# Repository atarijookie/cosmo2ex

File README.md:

# Cosmo2ex
This is a continuation / evolution of CosmosEx device. It is an ACSI/SCSI hard drive emulator, floppy emulator, IKBD emulator for Atari 16/32 Bit range of computers

Open design, non-commercial license - see [License](#license).

# What's what

- ce_cores - this is the network server to which the device connects to
- ce_dd_bootsectors	- ACSI/SCSI boot sectors
- ce_dd_prg	- driver for translated/network drives, date setting and screenshots
- android - Android app for switching floppy images from a phone, with a home screen widget
- docker - build and run scripts for ce_cores and webserver running in docker container
- release - builds tarballs + install script for installing directly on a Linux machine (systemd service)
- webserver - a configuration interface via browser

- libacsiscsi - library for access to ACSI/SCSI interface via few functions
- libdospath - long-to-short filename conversion library, emulating DOS paths (8.3)

- test_ce	- Atari test tools, all built into a single app (ce_tests.tos) with a menu to pick the test:
  - test_acsi	- Atari ACSI/SCSI transfer tester
  - test_filesystem	- Atari filesystem tester
  - test_floppy	- Atari floppy emulation tester
  - test_floppy_read	- Atari another floppy emulation tester
  - test_ikbd	- Atari IKBD injection chain tester
  - test_manual, test_manual2	- Atari another ACSI/SCSI transfer testers
  - test_rw, test_rw_user	- Atari ACSI write/read verification testers

# Android floppy app

`android/` is an app for switching floppy images from a phone, with a home screen widget. `android/build.sh` builds it in
docker into `webserver/static/app/`; users get it and connect it on the webserver's Settings → Android app. See `android/README.md`.

# Unit tests

`make test` runs all of them (see the top level `Makefile`, CI runs the same in `.github/workflows/ci.yml`).

- Linux: needs `g++`, `make`, `go` and the `libudev-dev` + `libevdev-dev` packages
- Windows: install [Cygwin](https://www.cygwin.com/) with the `gcc-g++` and `make` packages, then in the Cygwin shell:

      make -C libdospath test
      make -C ce_cores test

  Check out the repository with LF line endings (`git config --global core.autocrlf input` before cloning).
- macOS: needs the Xcode command line tools (`xcode-select --install`), then the same two `make` commands as for Windows

The file tests create their files in `/tmp`. Set `CE_TEST_TMPDIR` to run them on another filesystem, e.g. a
case-insensitive one (like APFS on macOS, FAT or NTFS): `CE_TEST_TMPDIR=/mnt/usb make -C libdospath test`.

# License

Cosmo2ex is open design, non-commercial license: the sources and the hardware designs are public, you can build
it, change it and share it for non-commercial use, but not sell it.

- software and firmware - [PolyForm Noncommercial License 1.0.0](LICENSE)
- hardware designs (schematics, PCBs in `devices/`) - [CC BY-NC-SA 4.0](devices/LICENSE)
- third party code keeps its own license (`third_party/`, and the files that say so in their header)

Building devices for yourself or your friends is fine. Selling devices, kits, PCBs or flashed boards needs a written
commercial license from the author - get in touch first (https://joo.kie.sk).

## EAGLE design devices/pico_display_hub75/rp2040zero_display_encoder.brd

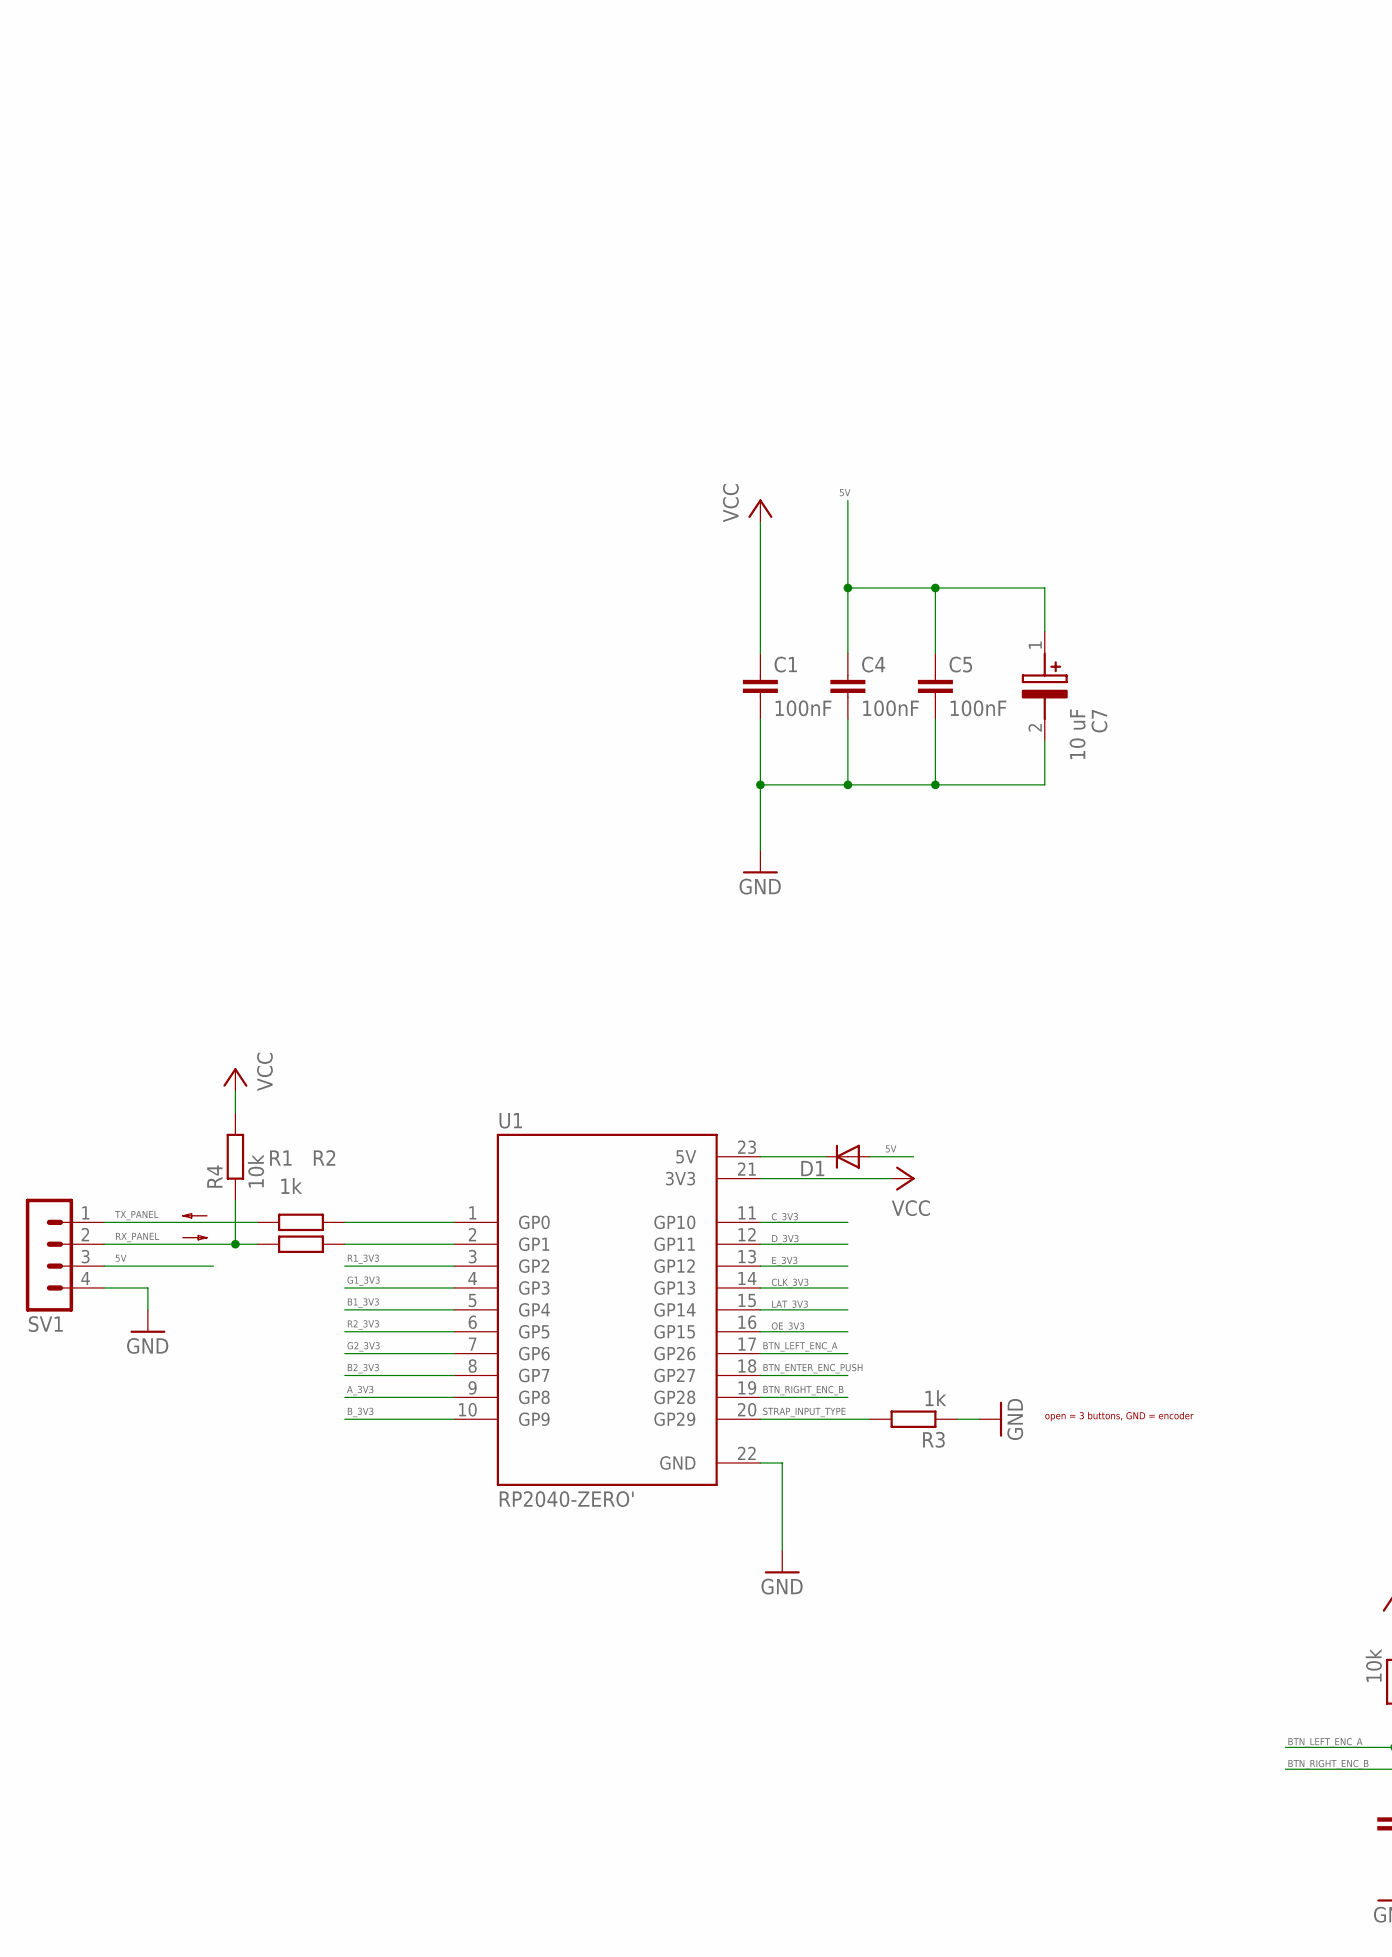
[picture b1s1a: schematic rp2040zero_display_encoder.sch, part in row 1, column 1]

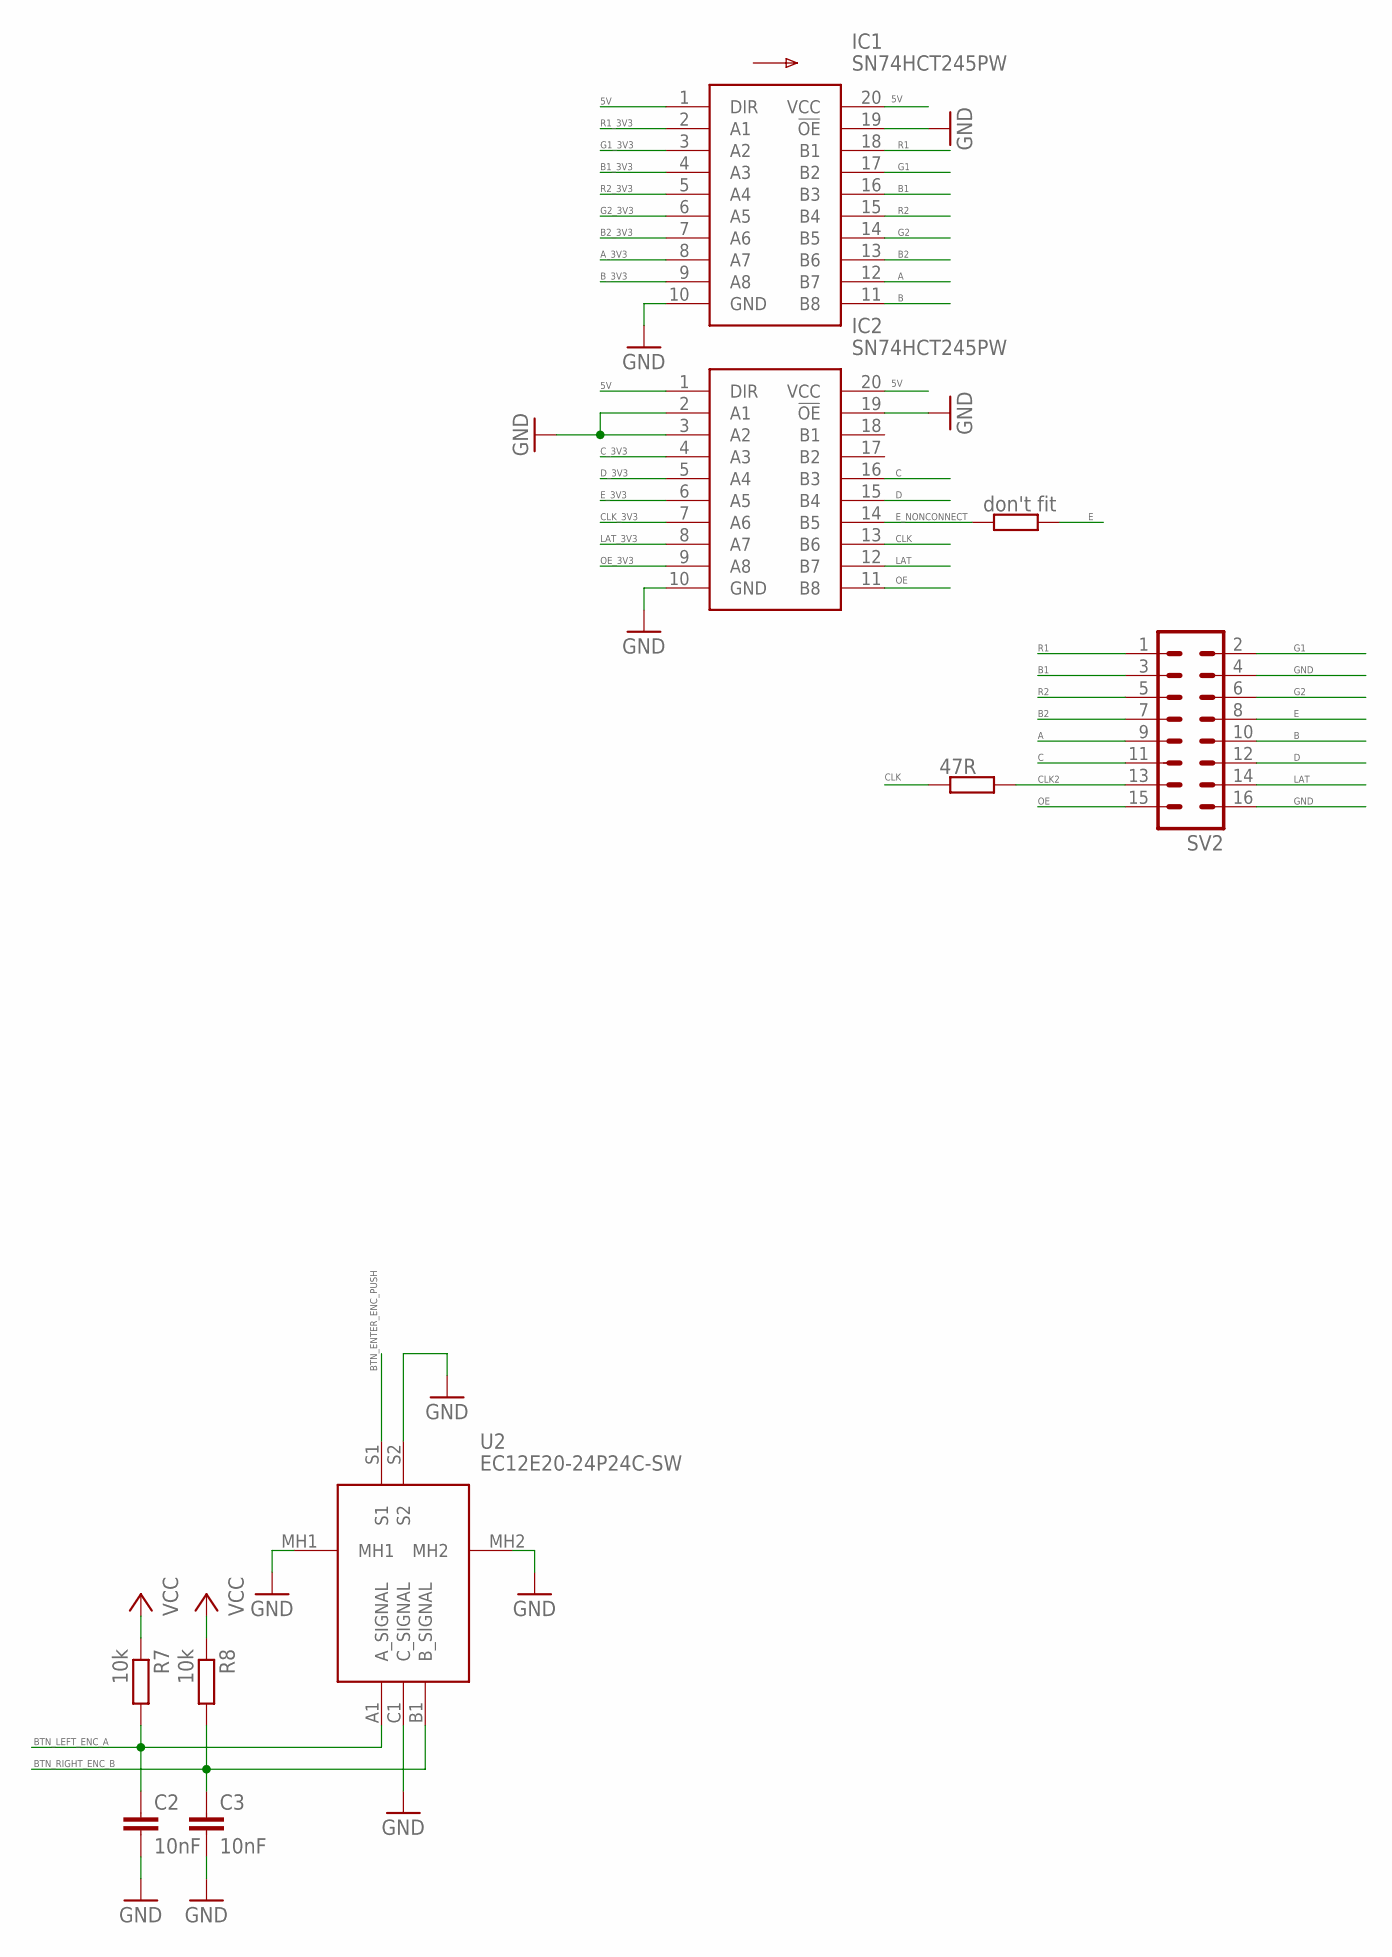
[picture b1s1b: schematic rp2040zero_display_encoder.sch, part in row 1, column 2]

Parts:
C1, C4, C5: 100nF; C0603
C2, C3: 10nF; C0603
C7: 10 uF; CAPPM3528X210N
D1: SK110-DIO; DO214AC
IC1, IC2: SN74HCT245PW; SOP65P640X120-20N
R1, R2, R3: 1k; R0603
R4, R7, R8: 10k; R0603
R5: don't fit; R0603
R6: 47R; R0603
SV1: MA04-1
SV2: ML16
U1: RP2040-ZERO'; MODULE_RP2040-ZERO
U2: EC12E20-24P24C-SW; EC12E2024P24CSW

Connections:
5V: C4.1, C5.1, C7.1 (+), D1.A, IC1.1 (DIR), IC1.20 (VCC), IC2.1 (DIR), IC2.20 (VCC), SV1.3
A: IC1.12 (B7), SV2.9
A_3V3: IC1.8 (A7), U1.9 (GP8)
B: IC1.11 (B8), SV2.10
B1: IC1.16 (B3), SV2.3
B1_3V3: IC1.4 (A3), U1.5 (GP4)
B2: IC1.13 (B6), SV2.7
B2_3V3: IC1.7 (A6), U1.8 (GP7)
BTN_ENTER_ENC_PUSH: U1.18 (GP27), U2.S1
BTN_LEFT_ENC_A: C2.1, R7.2, U1.17 (GP26), U2.A1 (A_SIGNAL)
BTN_RIGHT_ENC_B: C3.1, R8.2, U1.19 (GP28), U2.B1 (B_SIGNAL)
B_3V3: IC1.9 (A8), U1.10 (GP9)
C: IC2.16 (B3), SV2.11
CLK: IC2.13 (B6), R6.1
CLK2: R6.2, SV2.13
CLK_3V3: IC2.7 (A6), U1.14 (GP13)
C_3V3: IC2.4 (A3), U1.11 (GP10)
D: IC2.15 (B4), SV2.12
D_3V3: IC2.5 (A4), U1.12 (GP11)
E: R5.2, SV2.8
E_3V3: IC2.6 (A5), U1.13 (GP12)
E_NONCONNECT: IC2.14 (B5), R5.1
G1: IC1.17 (B2), SV2.2
G1_3V3: IC1.3 (A2), U1.4 (GP3)
G2: IC1.14 (B5), SV2.6
G2_3V3: IC1.6 (A5), U1.7 (GP6)
GND: C1.2, C2.2, C3.2, C4.2, C5.2, C7.2 (-), IC1.10 (GND), IC1.19 (!OE), IC2.2 (A1), IC2.3 (A2), IC2.10 (GND), IC2.19 (!OE), R3.1, SV1.4, SV2.4, SV2.16, U1.22 (GND), U2.C1 (C_SIGNAL), U2.MH1, U2.MH2, U2.S2
LAT: IC2.12 (B7), SV2.14
LAT_3V3: IC2.8 (A7), U1.15 (GP14)
unnamed: R1.2, U1.1 (GP0)
unnamed: R2.2, U1.2 (GP1)
unnamed: D1.C, U1.23 (5V)
OE: IC2.11 (B8), SV2.15
OE_3V3: IC2.9 (A8), U1.16 (GP15)
R1: IC1.18 (B1), SV2.1
R1_3V3: IC1.2 (A1), U1.3 (GP2)
R2: IC1.15 (B4), SV2.5
R2_3V3: IC1.5 (A4), U1.6 (GP5)
RX_PANEL: R2.1, R4.1, SV1.2
STRAP_INPUT_TYPE: R3.2, U1.20 (GP29)
TX_PANEL: R1.1, SV1.1
VCC: C1.1, R4.2, R7.1, R8.1, U1.21 (3V3)

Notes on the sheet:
open = 3 buttons, GND = encoder

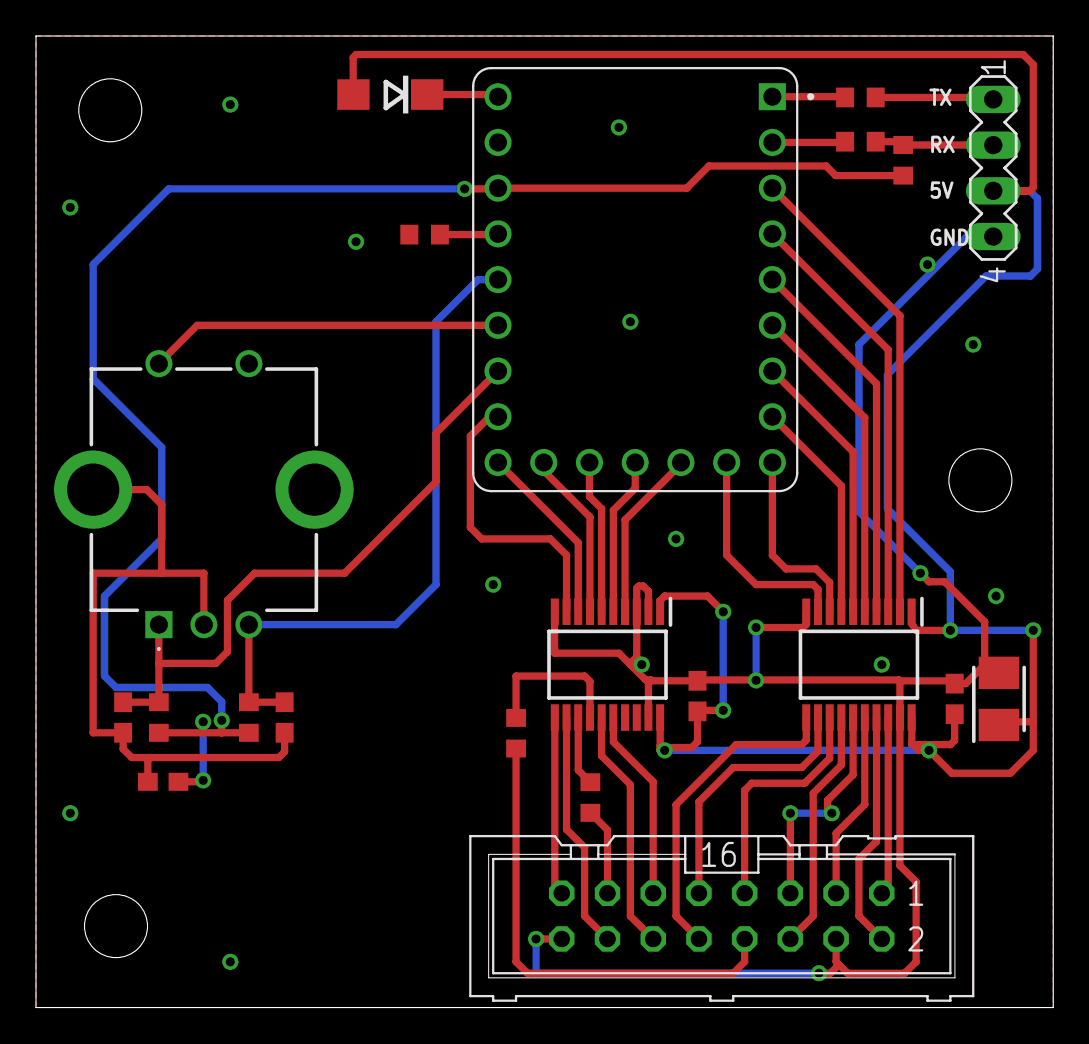
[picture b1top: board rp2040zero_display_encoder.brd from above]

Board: 2 copper layers, 56.5 x 54.0 mm, 21 parts (0 on the bottom side), 42 nets.

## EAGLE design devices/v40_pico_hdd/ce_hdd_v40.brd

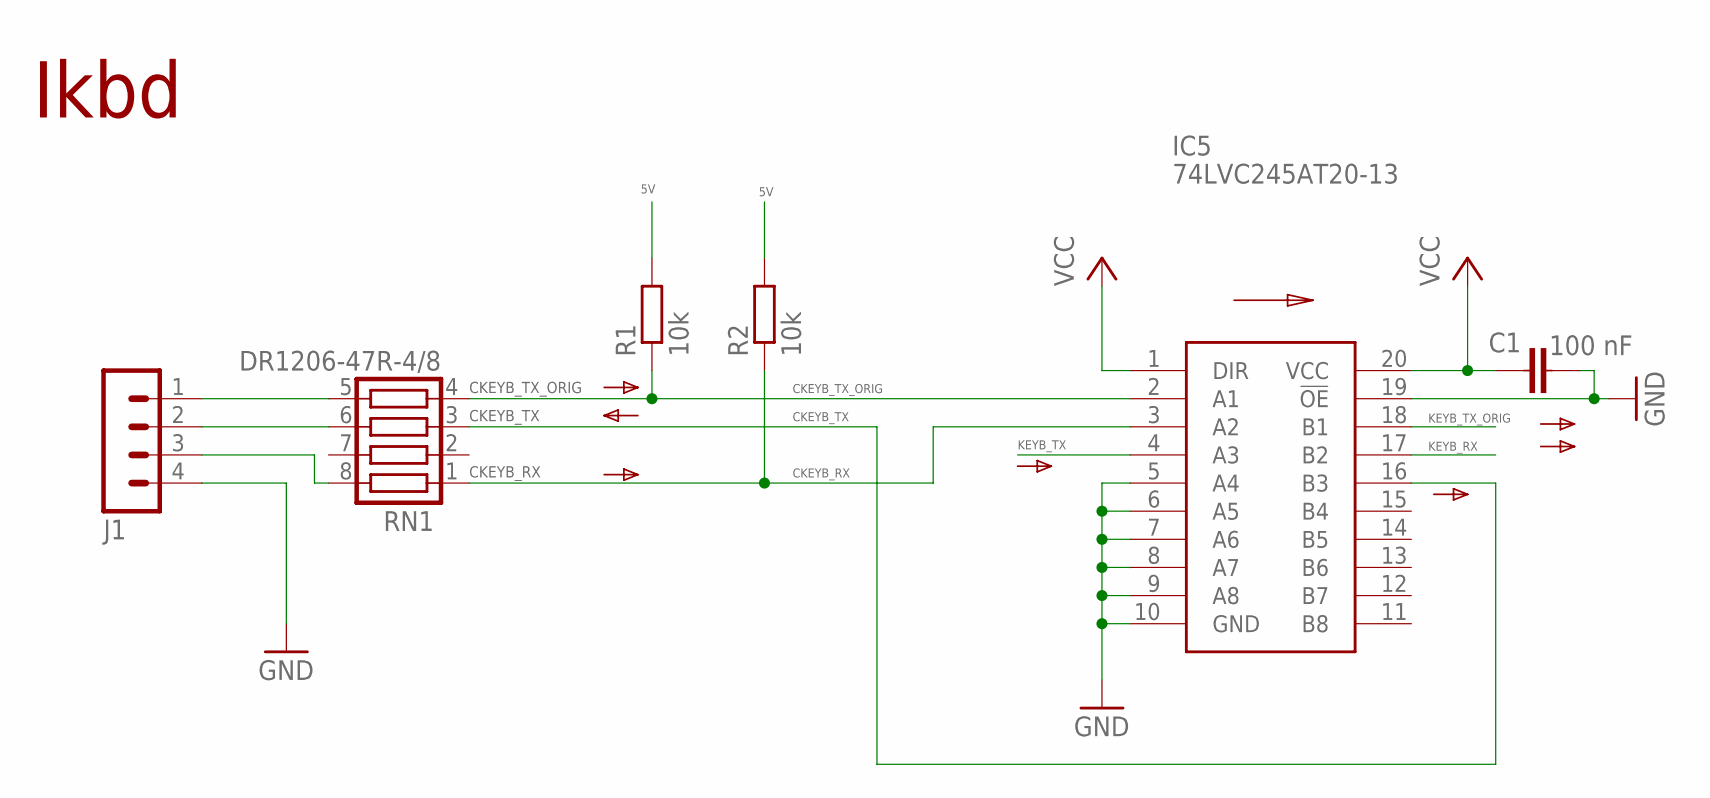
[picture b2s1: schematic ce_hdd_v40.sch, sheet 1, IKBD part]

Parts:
C1: 100 nF; C0603
IC5: 74LVC245AT20-13; SOP65P640X120-20N
J1: MA04-1
R1, R2: 10k; R0603
RN1: DR1206-47R-4/8; CTS742C083

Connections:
5V: R1.2, R2.2; also elsewhere on the board
CKEYB_RX: IC5.3 (A2), R2.1, RN1.1
CKEYB_TX: IC5.16 (B3), RN1.3
CKEYB_TX_ORIG: IC5.2 (A1), R1.1, RN1.4
GND: C1.1, IC5.5 (A4), IC5.6 (A5), IC5.7 (A6), IC5.8 (A7), IC5.9 (A8), IC5.10 (GND), IC5.19 (!OE), J1.4; also elsewhere on the board
KEYB_RX: IC5.17 (B2); also elsewhere on the board
KEYB_TX: IC5.4 (A3); also elsewhere on the board
KEYB_TX_ORIG: IC5.18 (B1); also elsewhere on the board
unnamed: J1.2, RN1.6
VCC: C1.2, IC5.1 (DIR), IC5.20 (VCC); also elsewhere on the board
ZKEYB_RX: J1.3, RN1.8
ZKEYB_TX_ORIG: J1.1, RN1.5

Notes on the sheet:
Ikbd

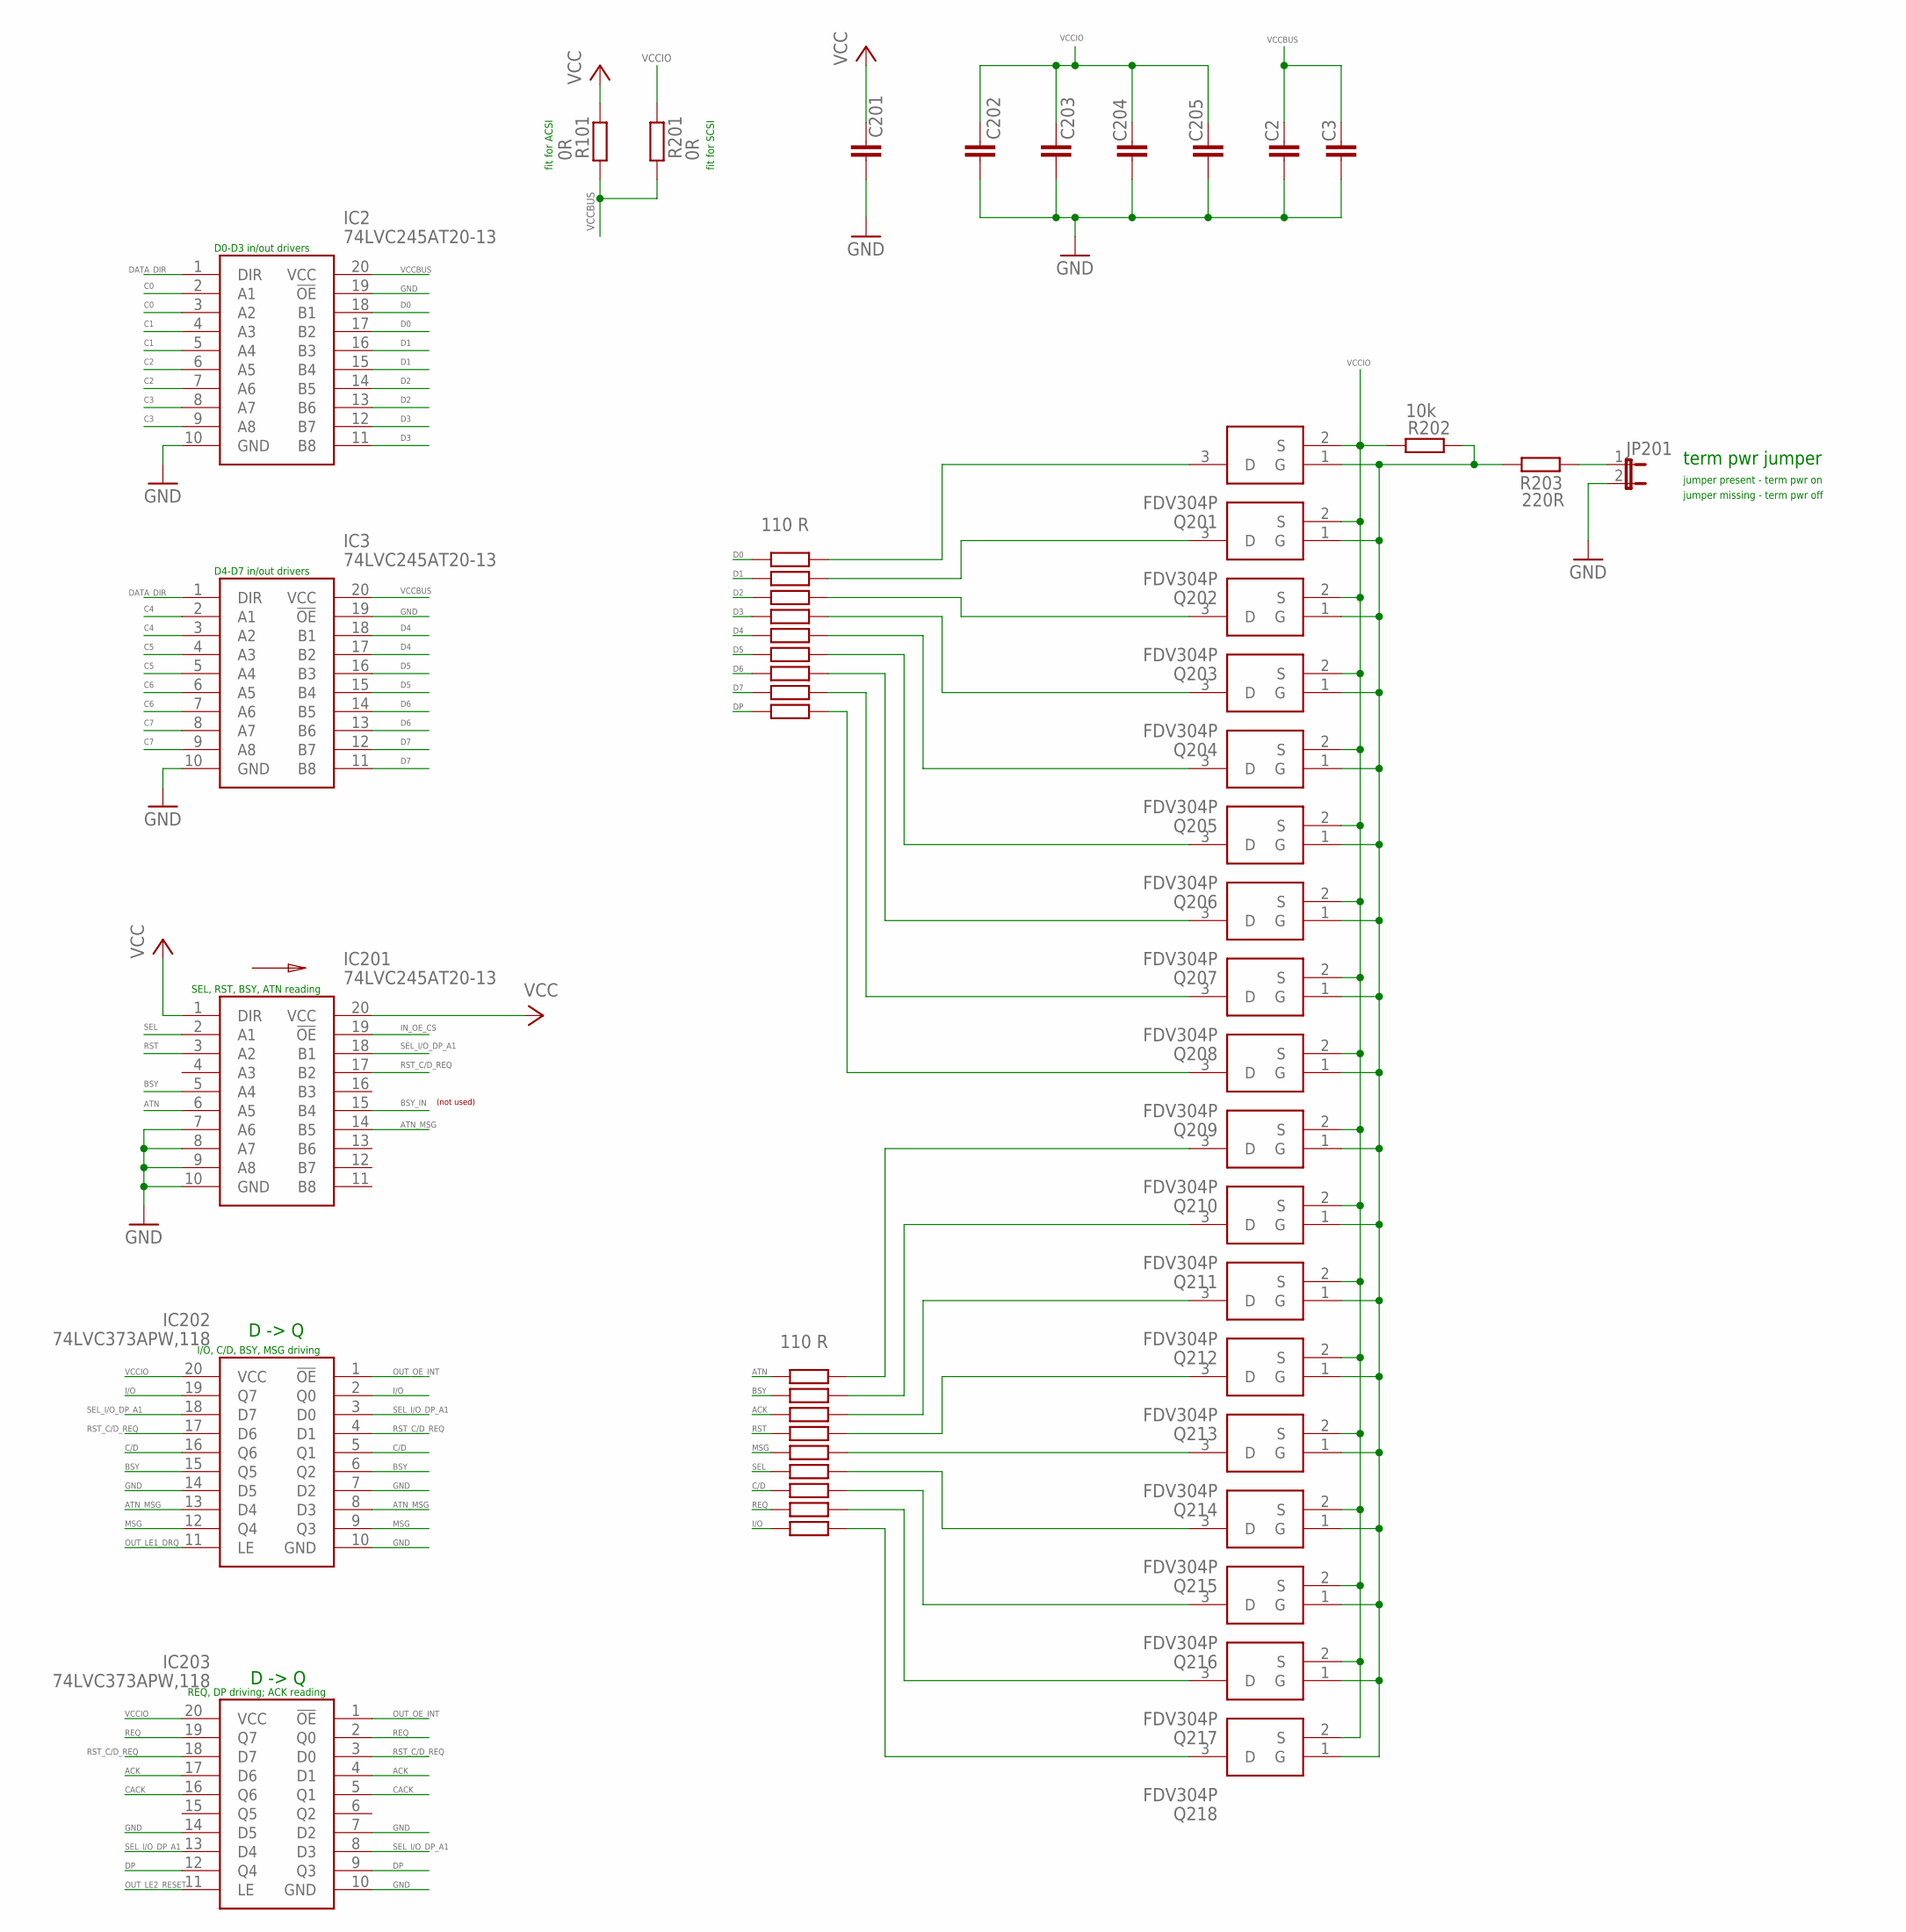
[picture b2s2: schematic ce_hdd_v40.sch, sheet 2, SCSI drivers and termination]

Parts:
C2, C3, C201, C202, C204, C205: 100 nF; C0603
C203: 1 uF; C0603
IC2, IC3, IC201: 74LVC245AT20-13; SOP65P640X120-20N
IC202, IC203: 74LVC373APW,118; SOP65P640X110-20N
JP201: JP1E; JP1
Q201, Q202, Q203, Q204, Q205, Q206, Q207, Q208, Q209, Q210, Q211, Q212, Q213, Q214, Q215, Q216, Q217, Q218: FDV304P; SOT95P237X112-3N
R101, R201: 0R; R0603
R202: 10k; R0603
R203: 220R; R0603
R204, R205, R206, R207, R208, R209, R210, R211, R212, R213, R214, R215, R216, R217, R218, R219, R220, R221: 110 R; R0603

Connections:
AAAA: Q201.3 (D), R204.1
ACK: IC203.4 (D1), IC203.17 (D6), R215.2; also elsewhere on the board
ATN: IC201.6 (A5), R213.2; also elsewhere on the board
ATN_MSG: IC201.14 (B5), IC202.8 (D3), IC202.13 (D4); also elsewhere on the board
BSY: IC201.5 (A4), IC202.6 (Q2), IC202.15 (Q5), R214.2; also elsewhere on the board
BSY_IN: IC201.15 (B4)
C0: IC2.2 (A1), IC2.3 (A2); also elsewhere on the board
C1: IC2.4 (A3), IC2.5 (A4); also elsewhere on the board
C2: IC2.6 (A5), IC2.7 (A6); also elsewhere on the board
C3: IC2.8 (A7), IC2.9 (A8); also elsewhere on the board
C4: IC3.2 (A1), IC3.3 (A2); also elsewhere on the board
C5: IC3.4 (A3), IC3.5 (A4); also elsewhere on the board
C6: IC3.6 (A5), IC3.7 (A6); also elsewhere on the board
C7: IC3.8 (A7), IC3.9 (A8); also elsewhere on the board
C/D: IC202.5 (Q1), IC202.16 (Q6), R219.2; also elsewhere on the board
CACK: IC203.5 (Q1), IC203.16 (Q6); also elsewhere on the board
D0: IC2.17 (B2), IC2.18 (B1), R204.2; also elsewhere on the board
D1: IC2.15 (B4), IC2.16 (B3), R205.2; also elsewhere on the board
D2: IC2.13 (B6), IC2.14 (B5), R206.2; also elsewhere on the board
D3: IC2.11 (B8), IC2.12 (B7), R207.2; also elsewhere on the board
D4: IC3.17 (B2), IC3.18 (B1), R208.2; also elsewhere on the board
D5: IC3.15 (B4), IC3.16 (B3), R209.2; also elsewhere on the board
D6: IC3.13 (B6), IC3.14 (B5), R210.2; also elsewhere on the board
D7: IC3.11 (B8), IC3.12 (B7), R211.2; also elsewhere on the board
DATA_DIR: IC2.1 (DIR), IC3.1 (DIR); also elsewhere on the board
DP: IC203.9 (Q3), IC203.12 (Q4), R212.2; also elsewhere on the board
GND: C2.2, C3.2, C201.2, C202.2, C203.2, C204.2, C205.2, IC2.10 (GND), IC2.19 (!OE), IC3.10 (GND), IC3.19 (!OE), IC201.7 (A6), IC201.8 (A7), IC201.9 (A8), IC201.10 (GND), IC202.7 (D2), IC202.10 (GND), IC202.14 (D5), IC203.7 (D2), IC203.10 (GND), IC203.14 (D5), JP201.2; also elsewhere on the board
I/O: IC202.2 (Q0), IC202.19 (Q7), R221.2; also elsewhere on the board
IN_OE_CS: IC201.19 (!OE); also elsewhere on the board
MSG: IC202.9 (Q3), IC202.12 (Q4), R217.2; also elsewhere on the board
unnamed: JP201.1, R203.2
unnamed: Q202.3 (D), R205.1
unnamed: Q203.3 (D), R206.1
unnamed: Q204.3 (D), R207.1
unnamed: Q205.3 (D), R208.1
unnamed: Q206.3 (D), R209.1
unnamed: Q207.3 (D), R210.1
unnamed: Q208.3 (D), R211.1
unnamed: Q209.3 (D), R212.1
unnamed: Q210.3 (D), R213.1
unnamed: Q211.3 (D), R214.1
unnamed: Q212.3 (D), R215.1
unnamed: Q213.3 (D), R216.1
unnamed: Q214.3 (D), R217.1
unnamed: Q215.3 (D), R218.1
unnamed: Q216.3 (D), R219.1
unnamed: Q217.3 (D), R220.1
unnamed: Q218.3 (D), R221.1
OUT_LE1_DRQ: IC202.11 (LE); also elsewhere on the board
OUT_LE2_RESET: IC203.11 (LE); also elsewhere on the board
OUT_OE_INT: IC202.1 (!OE), IC203.1 (!OE); also elsewhere on the board
REQ: IC203.2 (Q0), IC203.19 (Q7), R220.2; also elsewhere on the board
RST: IC201.3 (A2), R216.2; also elsewhere on the board
RST_C/D_REQ: IC201.17 (B2), IC202.4 (D1), IC202.17 (D6), IC203.3 (D0), IC203.18 (D7); also elsewhere on the board
SEL: IC201.2 (A1), R218.2; also elsewhere on the board
SEL_I/O_DP_A1: IC201.18 (B1), IC202.3 (D0), IC202.18 (D7), IC203.8 (D3), IC203.13 (D4); also elsewhere on the board
TP_ON: Q201.1 (G), Q202.1 (G), Q203.1 (G), Q204.1 (G), Q205.1 (G), Q206.1 (G), Q207.1 (G), Q208.1 (G), Q209.1 (G), Q210.1 (G), Q211.1 (G), Q212.1 (G), Q213.1 (G), Q214.1 (G), Q215.1 (G), Q216.1 (G), Q217.1 (G), Q218.1 (G), R202.2, R203.1
VCC: C201.1, IC201.1 (DIR), IC201.20 (VCC), R101.2; also elsewhere on the board
VCCBUS: C2.1, C3.1, IC2.20 (VCC), IC3.20 (VCC), R101.1, R201.1
VCCIO: C202.1, C203.1, C204.1, C205.1, IC202.20 (VCC), IC203.20 (VCC), Q201.2 (S), Q202.2 (S), Q203.2 (S), Q204.2 (S), Q205.2 (S), Q206.2 (S), Q207.2 (S), Q208.2 (S), Q209.2 (S), Q210.2 (S), Q211.2 (S), Q212.2 (S), Q213.2 (S), Q214.2 (S), Q215.2 (S), Q216.2 (S), Q217.2 (S), Q218.2 (S), R201.2, R202.1; also elsewhere on the board

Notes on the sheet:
D -> Q
term pwr jumper
jumper present - term pwr on
jumper missing - term pwr off
D0-D3 in/out drivers
D4-D7 in/out drivers
SEL, RST, BSY, ATN reading
I/O, C/D, BSY, MSG driving
REQ, DP driving; ACK reading
(not used)
fit for ACSI
fit for SCSI

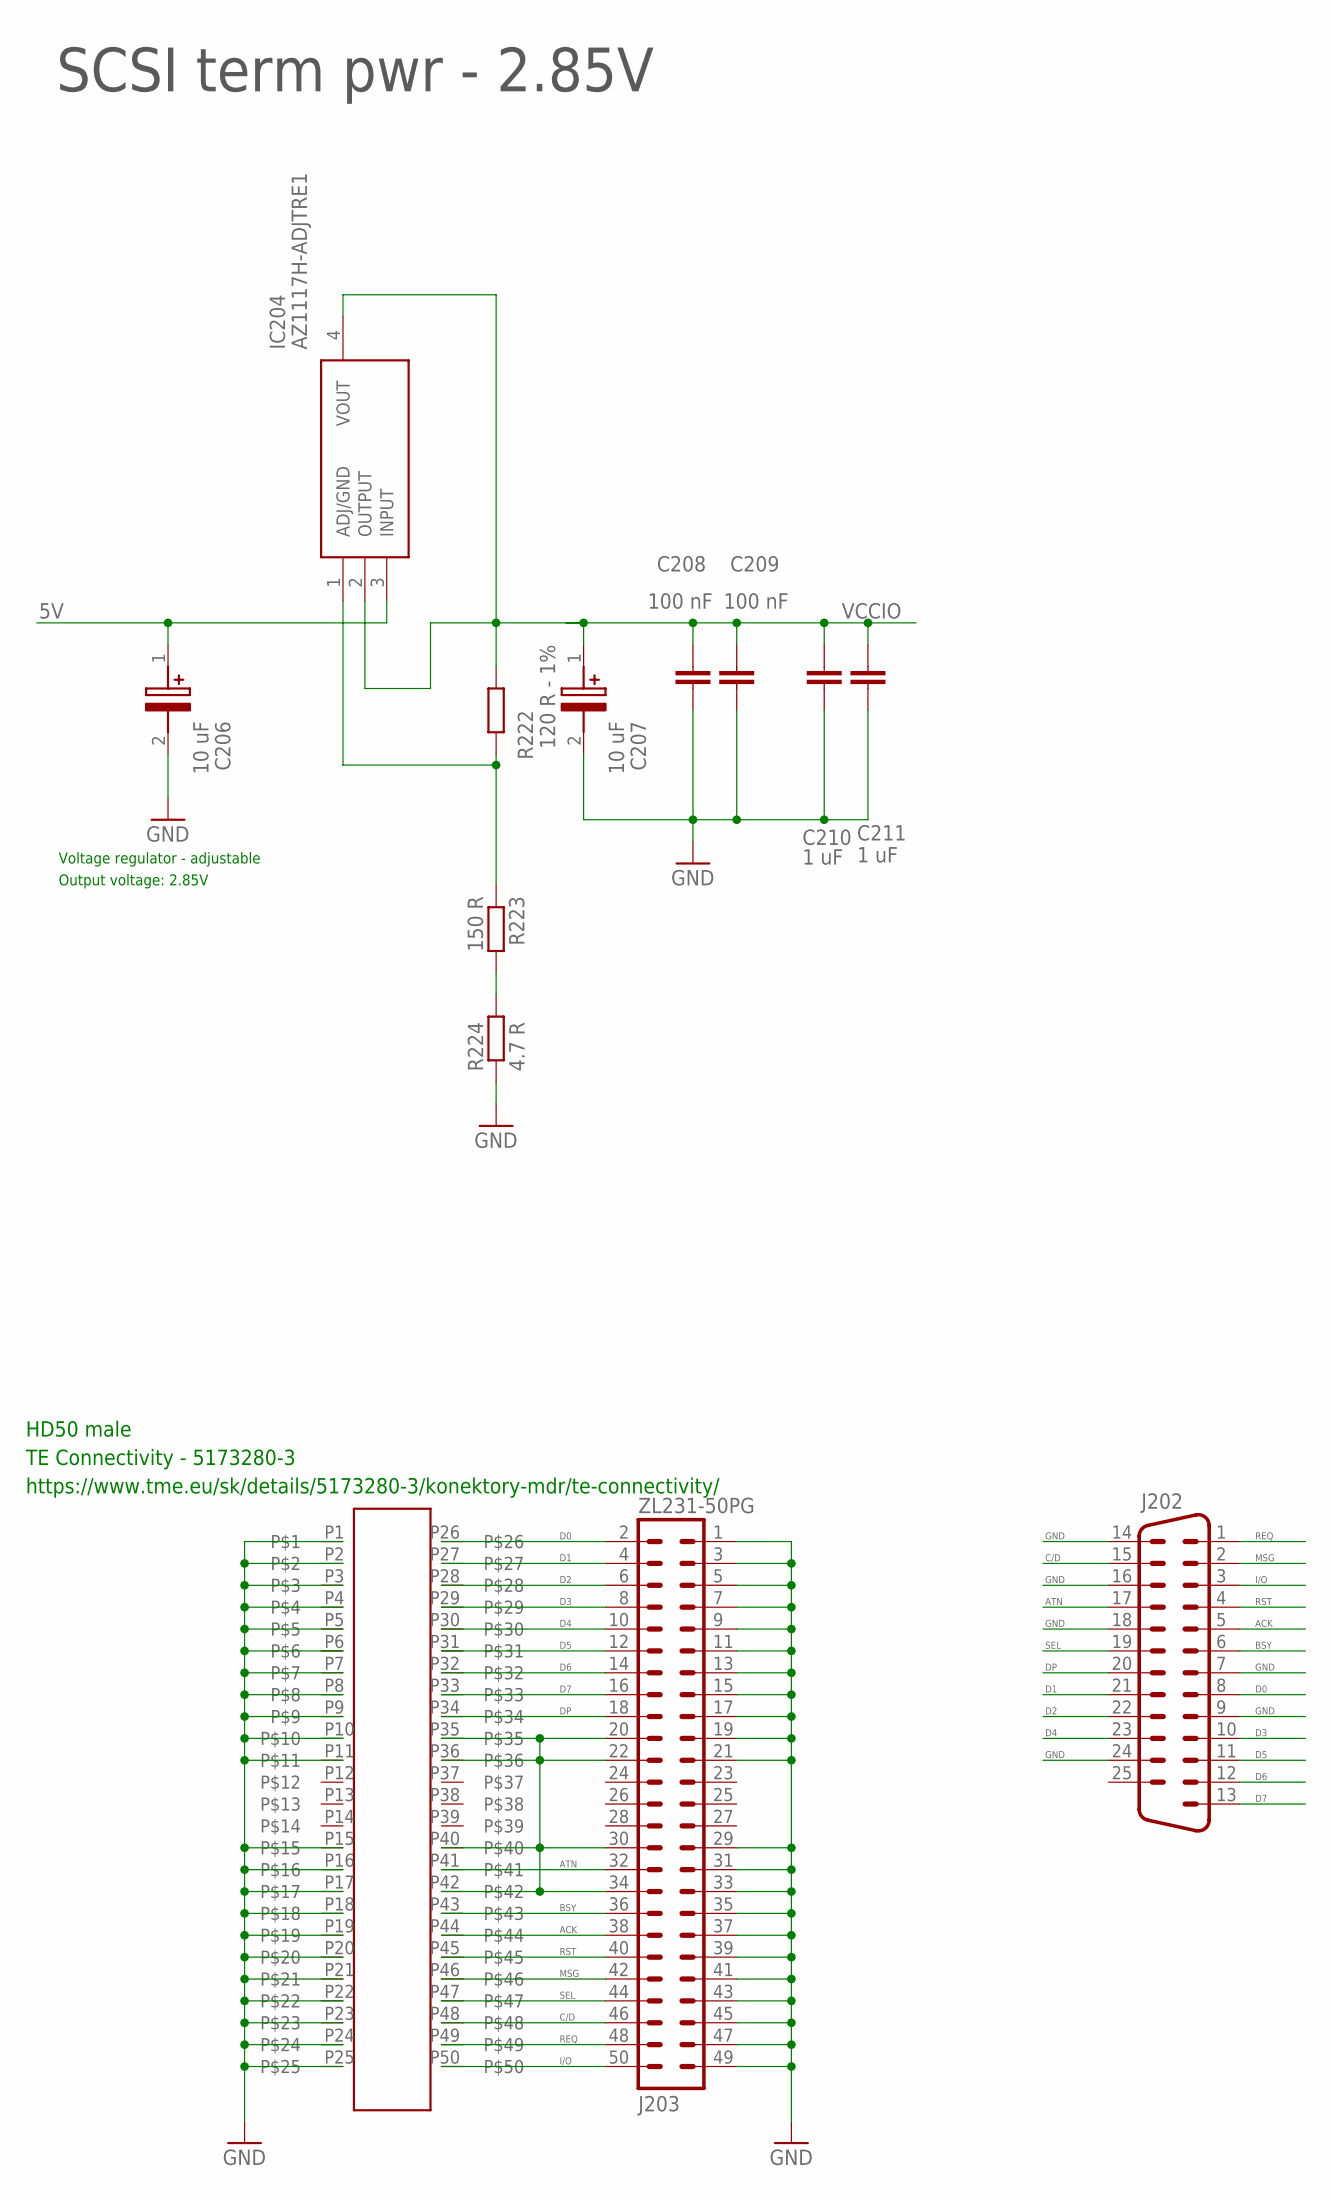
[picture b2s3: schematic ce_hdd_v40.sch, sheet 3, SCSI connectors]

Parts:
C206, C207: 10 uF; CAPPM3528X210N; MANUFACTURER_PART_NUMBER 293D106X9016B2TE3
C208, C209: 100 nF; C0603
C210, C211: 1 uF; C0603
IC204: AZ1117H-ADJTRE1; SOT230P700X185-4N
J201: TE Connectivity - 5173280-3; HD50_MALE
J202: M25V
J203: ZL231-50PG; ML50
R222: 120 R - 1%; R0603
R223: 150 R; R0603
R224: 4.7 R; R0603

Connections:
5V: C206.1 (+), IC204.3 (INPUT); also elsewhere on the board
ACK: J201.P44, J202.5, J203.38; also elsewhere on the board
ATN: J201.P41, J202.17, J203.32; also elsewhere on the board
BSY: J201.P43, J202.6, J203.36; also elsewhere on the board
C/D: J201.P48, J202.15, J203.46; also elsewhere on the board
D0: J201.P26, J202.8, J203.2; also elsewhere on the board
D1: J201.P27, J202.21, J203.4; also elsewhere on the board
D2: J201.P28, J202.22, J203.6; also elsewhere on the board
D3: J201.P29, J202.10, J203.8; also elsewhere on the board
D4: J201.P30, J202.23, J203.10; also elsewhere on the board
D5: J201.P31, J202.11, J203.12; also elsewhere on the board
D6: J201.P32, J202.12, J203.14; also elsewhere on the board
D7: J201.P33, J202.13, J203.16; also elsewhere on the board
DP: J201.P34, J202.20, J203.18; also elsewhere on the board
GND: C206.2 (-), C207.2 (-), C208.2, C209.2, C210.2, C211.2, J201.P1, J201.P2, J201.P3, J201.P4, J201.P5, J201.P6, J201.P7, J201.P8, J201.P9, J201.P10, J201.P11, J201.P15, J201.P16, J201.P17, J201.P18, J201.P19, J201.P20, J201.P21, J201.P22, J201.P23, J201.P24, J201.P25, J201.P35, J201.P36, J201.P40, J201.P42, J202.7, J202.9, J202.14, J202.16, J202.18, J202.24, J203.1, J203.3, J203.5, J203.7, J203.9, J203.11, J203.13, J203.15, J203.17, J203.19, J203.20, J203.21, J203.22, J203.29, J203.30, J203.31, J203.33, J203.34, J203.35, J203.37, J203.39, J203.41, J203.43, J203.45, J203.47, J203.49, R224.1; also elsewhere on the board
I/O: J201.P50, J202.3, J203.50; also elsewhere on the board
MSG: J201.P46, J202.2, J203.42; also elsewhere on the board
unnamed: R223.2, R224.2
unnamed: IC204.1 (ADJ/GND), R222.2, R223.1
REQ: J201.P49, J202.1, J203.48; also elsewhere on the board
RST: J201.P45, J202.4, J203.40; also elsewhere on the board
SEL: J201.P47, J202.19, J203.44; also elsewhere on the board
VCCIO: C207.1 (+), C208.1, C209.1, C210.1, C211.1, IC204.2 (OUTPUT), IC204.4 (VOUT), R222.1; also elsewhere on the board

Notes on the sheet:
Voltage regulator - adjustable
Output voltage: 2.85V
SCSI term pwr - 2.85V
HD50 male
TE Connectivity - 5173280-3
https://www.tme.eu/sk/details/5173280-3/konektory-mdr/te-connectivity/
